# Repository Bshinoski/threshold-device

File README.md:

https://github.com/oduggan21/ThresholdDevice

Team Threshold
Ben Shinoski
Owen Duggan
Randall Reed

The repository is organized into 3 parts:
1. Documentation - Past deliverables/Information/Research
2. Hardware - Hardware related things including schematics/board layouts
3. Software - Software Code
4. Testing - Unit Tests and Integration Tests

Threshold is an innovative wearable device designed to enhance workout performance by detecting muscle failure in real time using an EMG sensor. Equipped with LED indicators and a rest timer, Threshold provides instant feedback to help users optimize their training. By delivering precise, data-driven insights, the device notifies users when they reach their threshold, ensuring they maximize each set and fully utilize their muscle capacity. This results in more effective workouts, improved performance, and safer training sessions.

test

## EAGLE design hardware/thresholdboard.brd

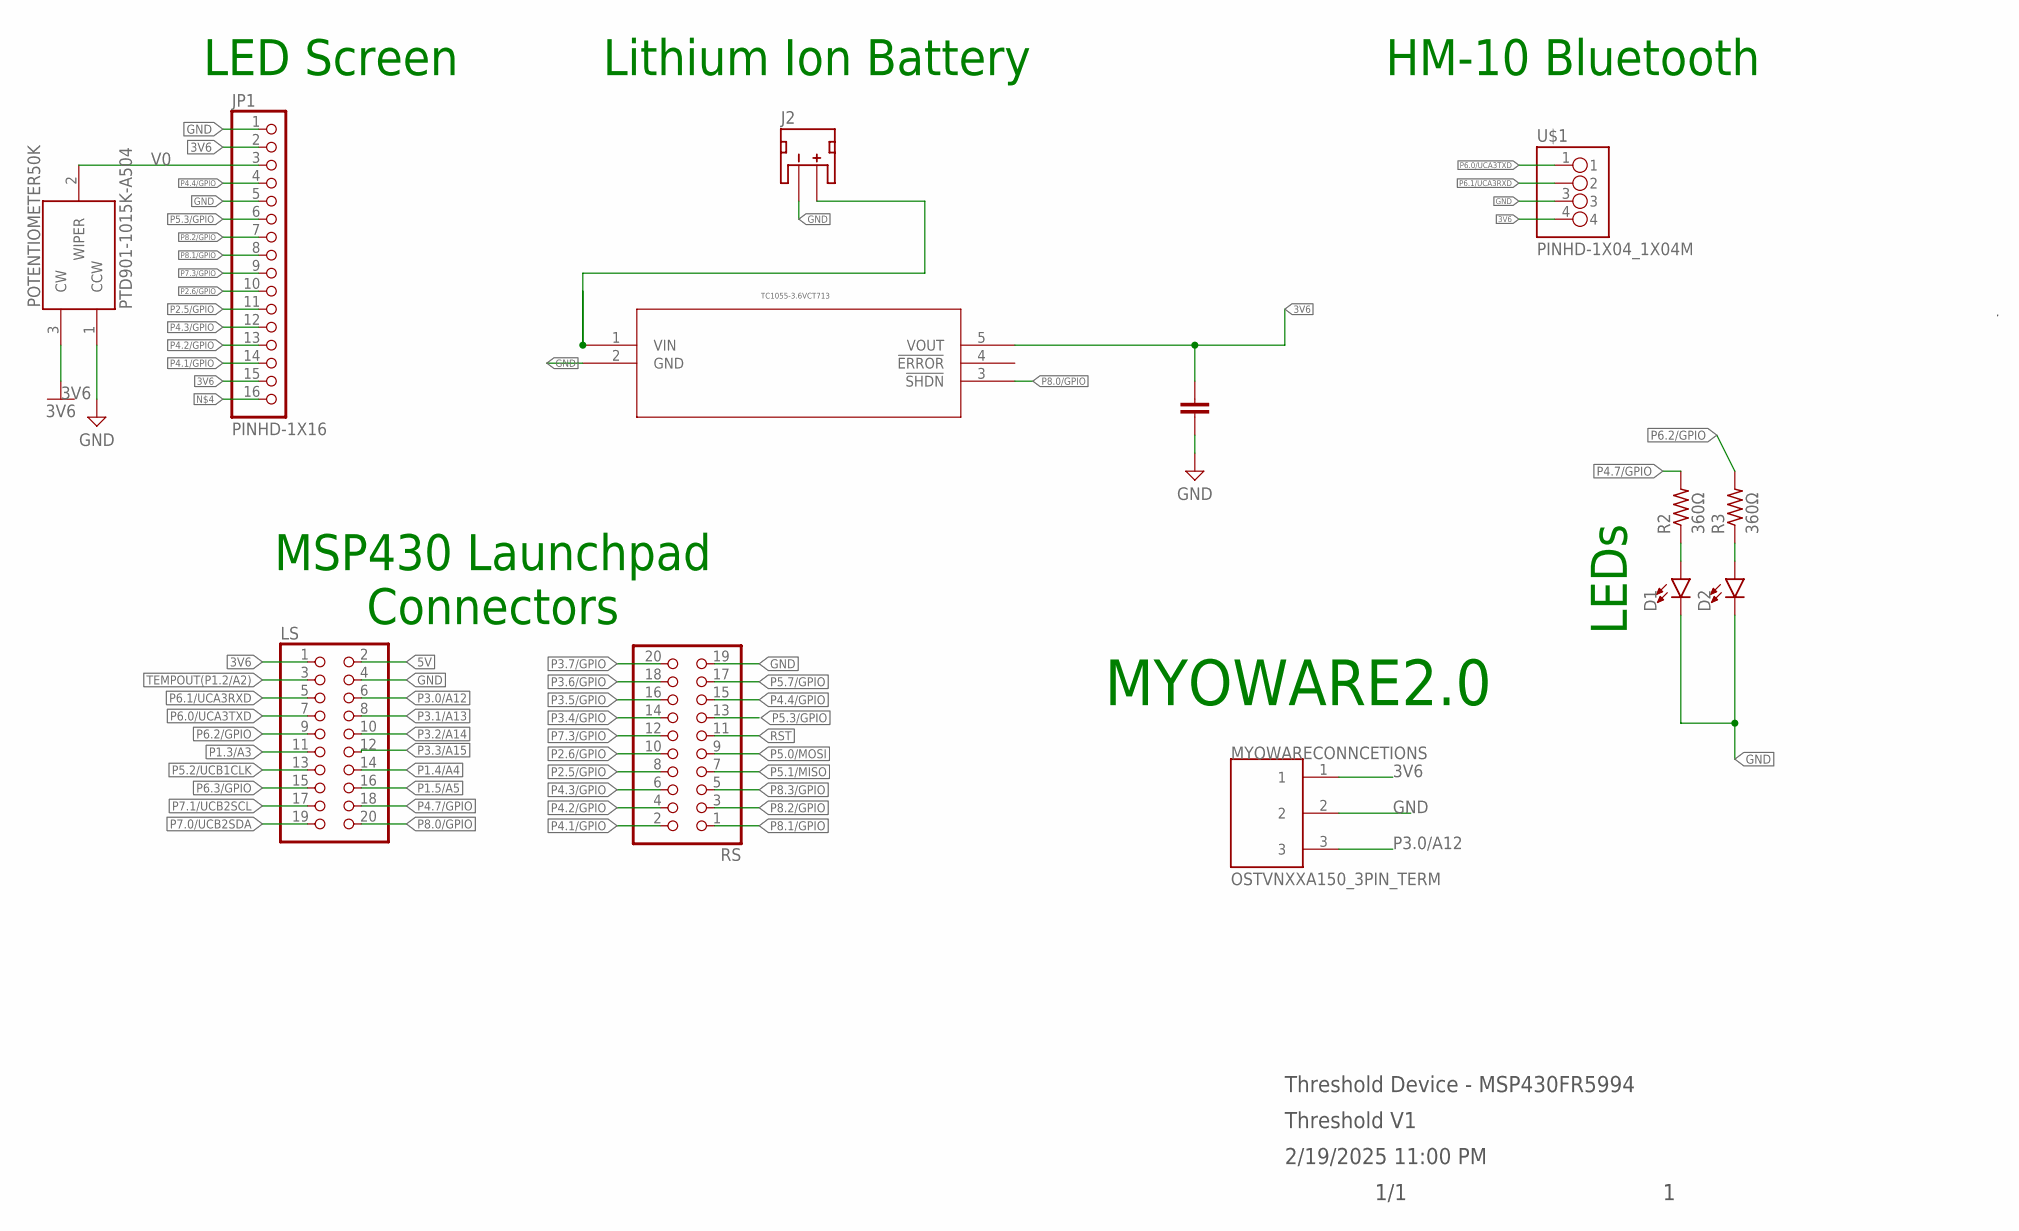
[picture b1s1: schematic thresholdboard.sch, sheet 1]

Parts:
C7: C_CHIP-0402(1005-METRIC); CAPC1005X60
D1, D2: LED3MM; LED_3MM
J2: JST_2MM_MALE; JST-2-SMD
JP1: PINHD-1X16; 1X16
LS: PINHD-2X10; 2X10
MYOWARECONNCETIONS: OSTVNXXA150_3PIN_TERM; OSTVNXXA150
POTENTIOMETER50K: PTD901-1015K-A504; PTD9011015KA504
R2, R3: 360Ω; R0805
RS: PINHD-2X10; 2X10
U1: TC1055-3.6VCT713; SOT-23-5_MC_MCH
U$1: PINHD-1X04_1X04M; 1X04

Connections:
3V6: C7.1, JP1.2, JP1.15, LS.1, MYOWARECONNCETIONS.1, POTENTIOMETER50K.3 (CW), U1.5 (VOUT), U$1.4
5V: LS.2
GND: C7.2, D1.K (C), D2.K (C), J2.1 (-), JP1.1, JP1.5, LS.4, MYOWARECONNCETIONS.2, POTENTIOMETER50K.1 (CCW), RS.19, U1.2 (GND), U$1.3
unnamed: D1.A, R2.1
unnamed: D2.A, R3.1
P1.3/A3: LS.11
P1.4/A4: LS.14
P1.5/A5: LS.16
P2.5/GPIO: JP1.11, RS.8
P2.6/GPIO: JP1.10, RS.10
P3.0/A12: LS.6, MYOWARECONNCETIONS.3
P3.1/A13: LS.8
P3.2/A14: LS.10
P3.3/A15: LS.12
P3.4/GPIO: RS.14
P3.5/GPIO: RS.16
P3.6/GPIO: RS.18
P3.7/GPIO: RS.20
P4.1/GPIO: JP1.14, RS.2
P4.2/GPIO: JP1.13, RS.4
P4.3/GPIO: JP1.12, RS.6
P4.4/GPIO: JP1.4, RS.15
P4.7/GPIO: LS.18, R2.2
P5.0/MOSI: RS.9
P5.1/MISO: RS.7
P5.2/UCB1CLK: LS.13
P5.3/GPIO: JP1.6, RS.13
P5.7/GPIO: RS.17
P6.0/UCA3TXD: LS.7, U$1.1
P6.1/UCA3RXD: LS.5, U$1.2
P6.2/GPIO: LS.9, R3.2
P6.3/GPIO: LS.15
P7.0/UCB2SDA: LS.19
P7.1/UCB2SCL: LS.17
P7.3/GPIO: JP1.9, RS.12
P8.0/GPIO: LS.20, U1.3 (!SHDN)
P8.1/GPIO: JP1.8, RS.1
P8.2/GPIO: JP1.7, RS.3
P8.3/GPIO: RS.5
RST: RS.11
TEMPOUT(P1.2/A2): LS.3
V0: JP1.3, POTENTIOMETER50K.2 (WIPER)
VIN: J2.2 (+), U1.1 (VIN)

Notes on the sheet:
LEDs
MSP430 Launchpad Connectors
LED Screen
Lithium Ion Battery
HM-10 Bluetooth
MYOWARE2.0
Threshold Device - MSP430FR5994
Threshold V1
2/19/2025 11:00 PM
1/1

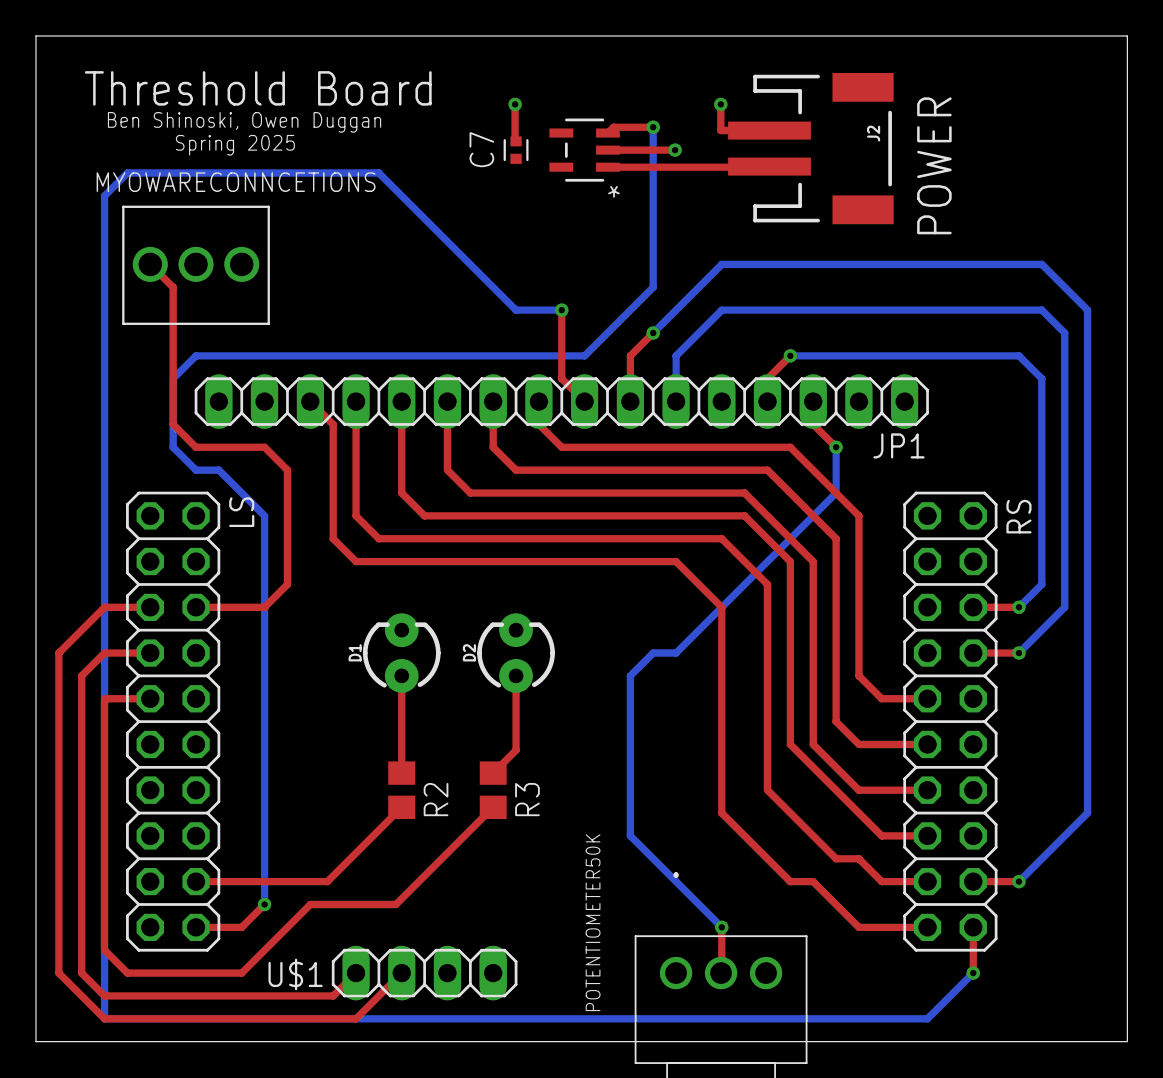
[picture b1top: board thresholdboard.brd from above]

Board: 2 copper layers, 60.6 x 55.9 mm, 13 parts (0 on the bottom side), 21 nets.

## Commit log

2025-08-26 Rename CPSC 4820 Deliverable #1.pdf to documentation/CPSC 4820 Deliverable #1.pdf
2025-08-26 Rename CPSC 4820 Deliverable #2 Document.pdf to documentation/CPSC 4820 Deliverable #2 Document.pdf
2025-08-26 Rename finalreport.pdf to documentation/finalreport.pdf
2025-08-26 Initial commit of Threshold Device project

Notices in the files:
parts and their libraries:
SparkFun-LED: Licensing: Creative Commons ShareAlike 4.0 International - https://creativecommons.org/licenses/by-sa/4.0
COPYRIGHT: Copyright (C) 2025 Ultra Librarian. All rights reserved.
